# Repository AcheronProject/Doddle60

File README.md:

# Acheron ISO60-SM-S-STM32-MX-TH-WI (Codename "Doddle60")

See [this page](https://gondolindrim.github.io/AcheronDocs/doddle60/intro.html) for the Doddle60PCB documentation.

## Introduction

**Doddle**. *British slang for something easily accomplished*.

The Doddle60 is a 60% plain-style PCB aimed at ISO layout users. It features minimal layout support and no LED backlight support. It runs an STM32F072 processor, USBC connector, ESD protection on both data lines and metallic case discharge, as well as overvoltage and overcurrent protection.

The layout was cherry-picked and hinited to me by Jae of the TopClack channel, an avid ISO user brit.

## Supported layouts

Click [this link](http://www.keyboard-layout-editor.com/#/gists/dfb069e34f7b14d63b03305a79dfc469) for the KLE file for the Doddle60.

## Renders

Click at the images to zoom in.

Renders generated by the [tracespace.io](https://tracespace.io/view/) site.

## Copyright notice

This project is released under the Acheron Open-Hardware License V1.1. For the license, please refer to the LICENCE.md file.

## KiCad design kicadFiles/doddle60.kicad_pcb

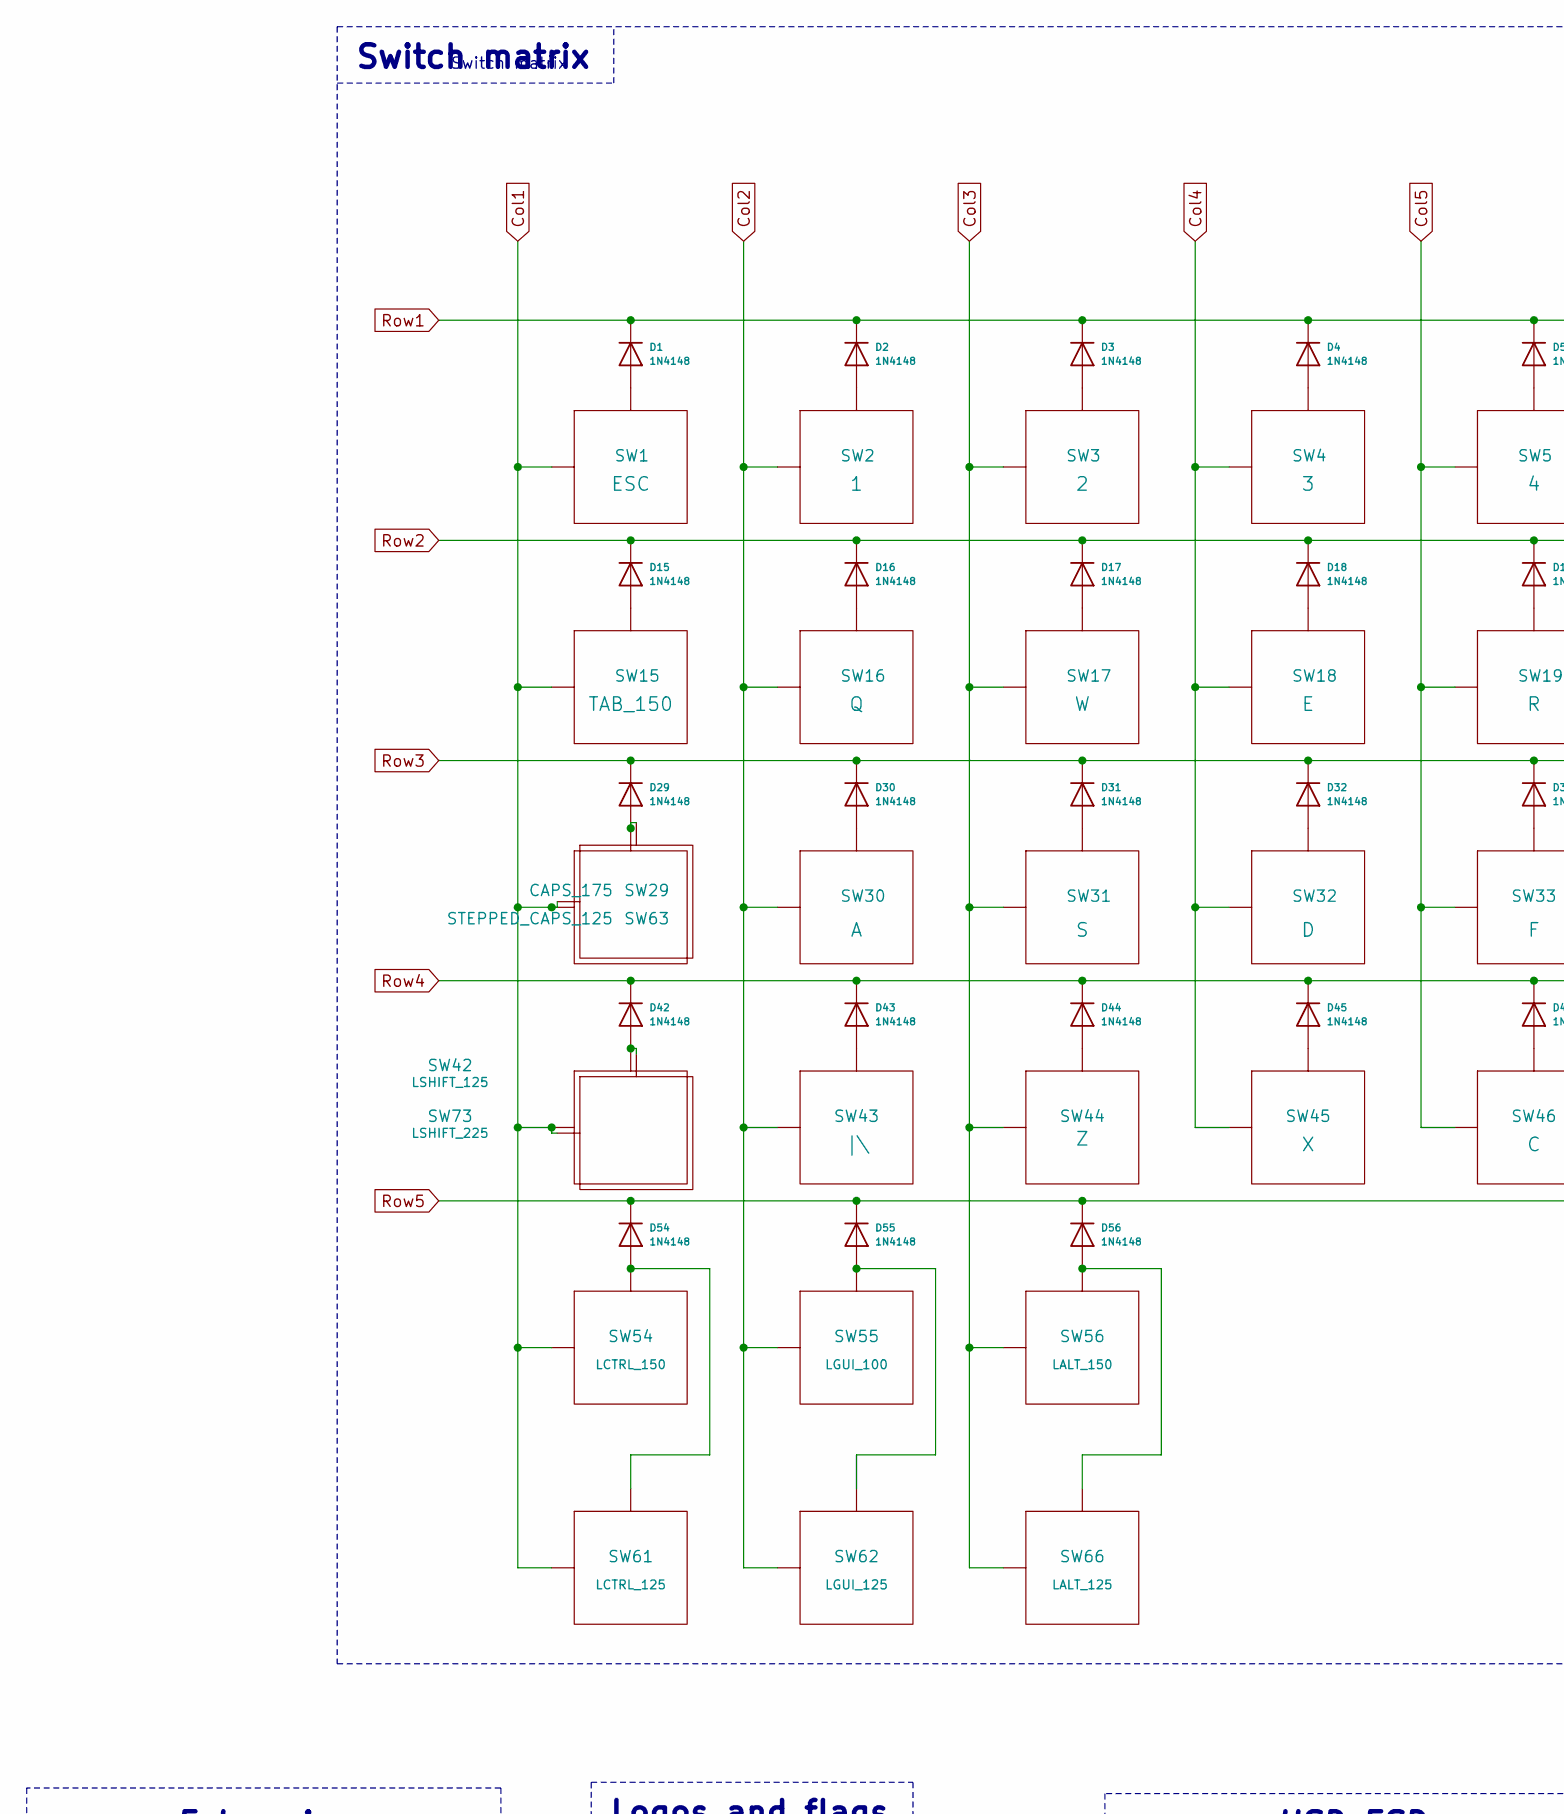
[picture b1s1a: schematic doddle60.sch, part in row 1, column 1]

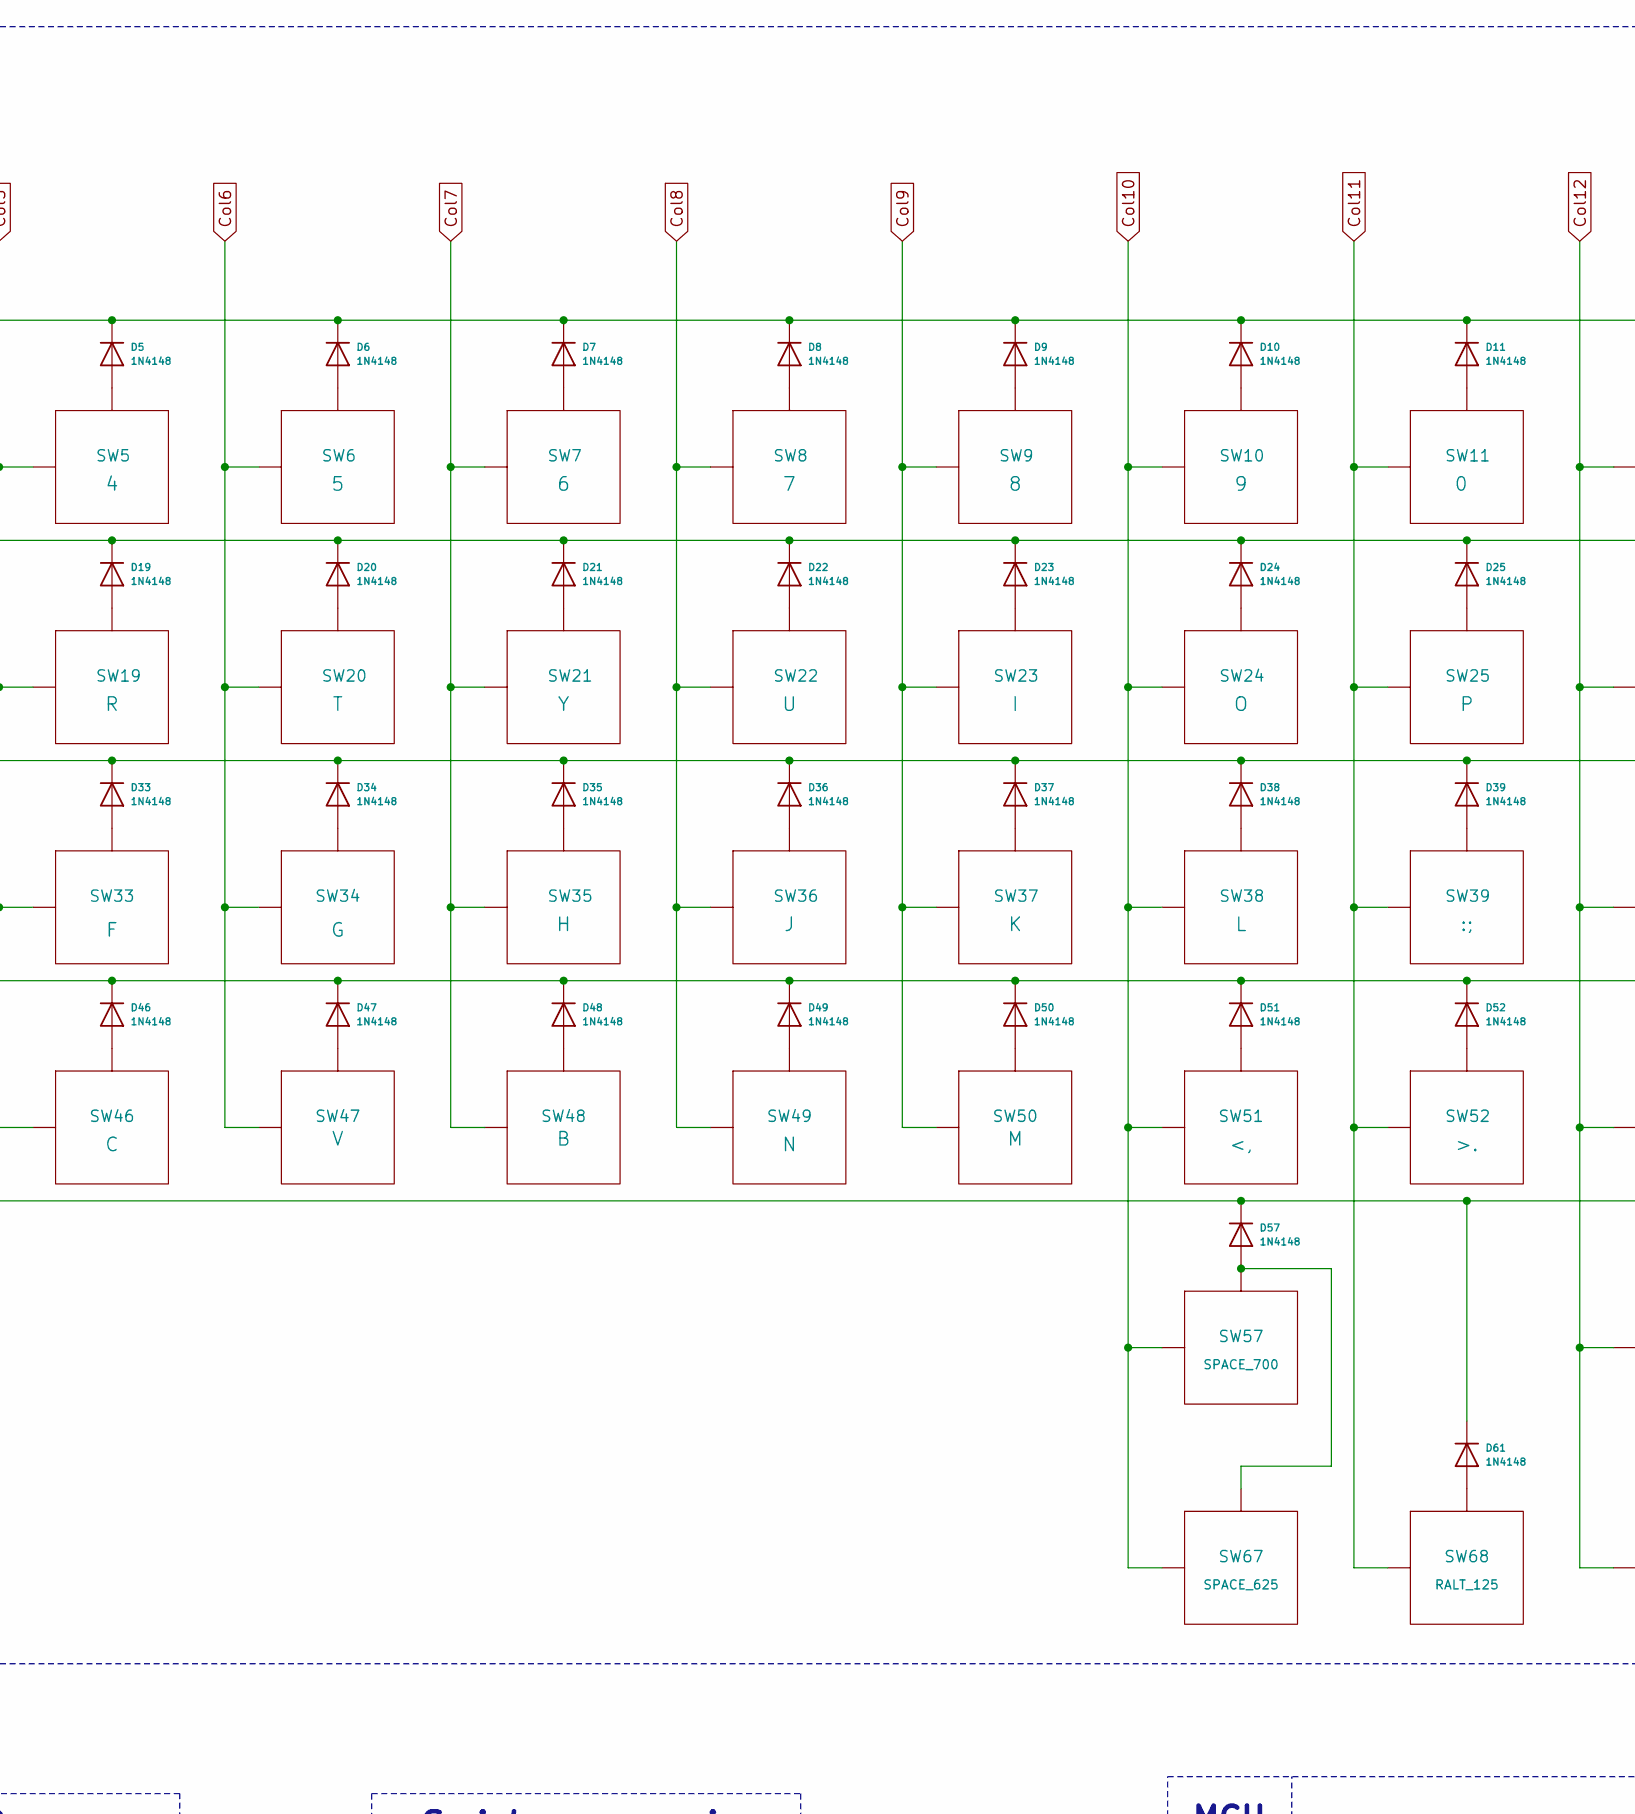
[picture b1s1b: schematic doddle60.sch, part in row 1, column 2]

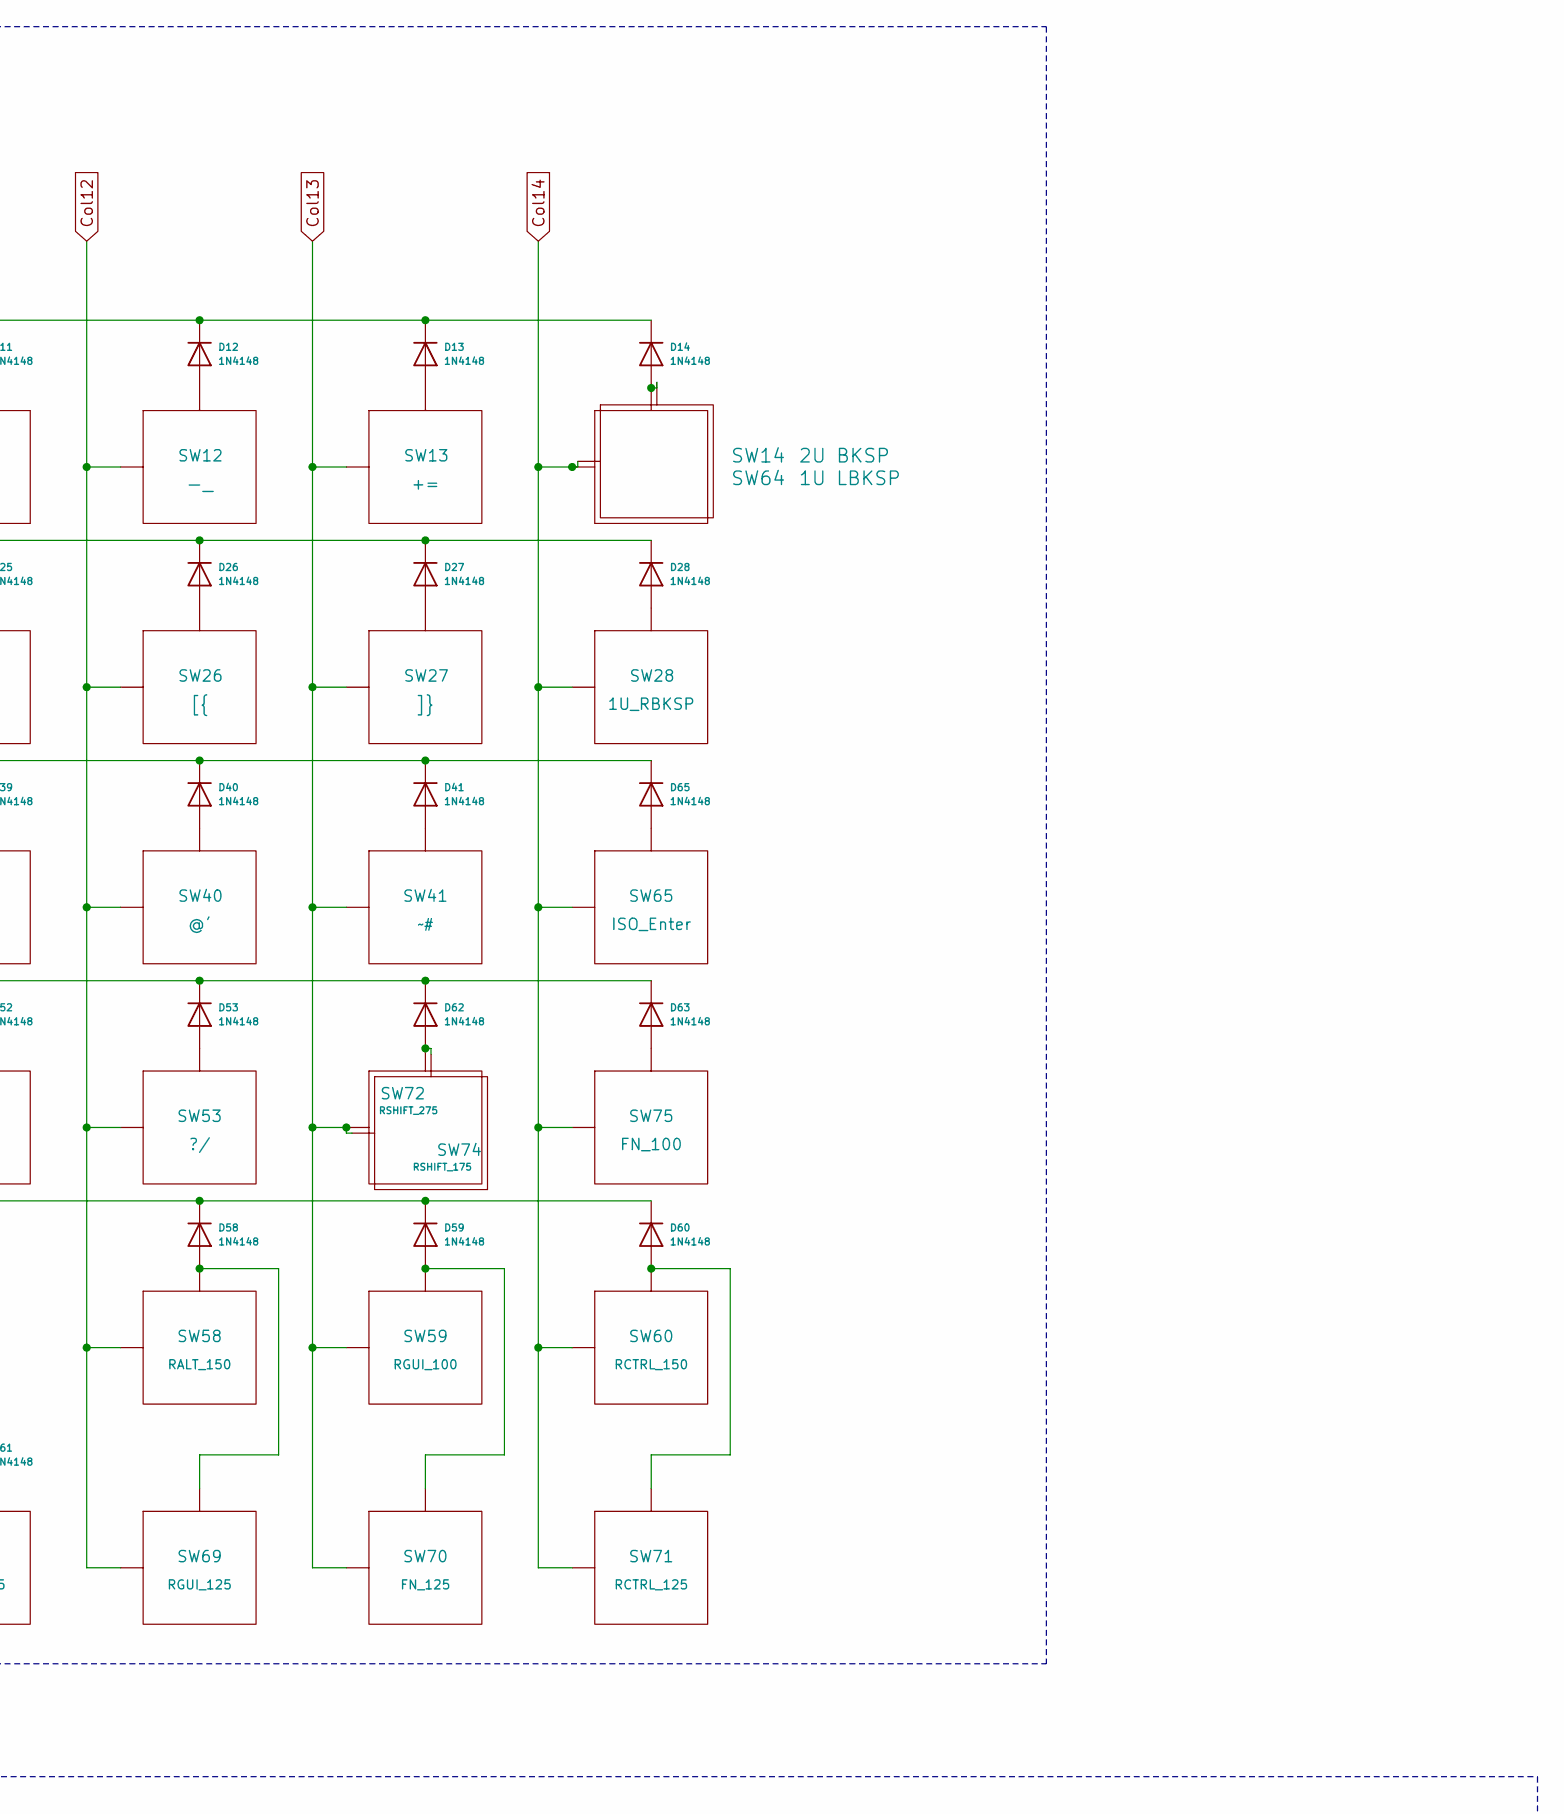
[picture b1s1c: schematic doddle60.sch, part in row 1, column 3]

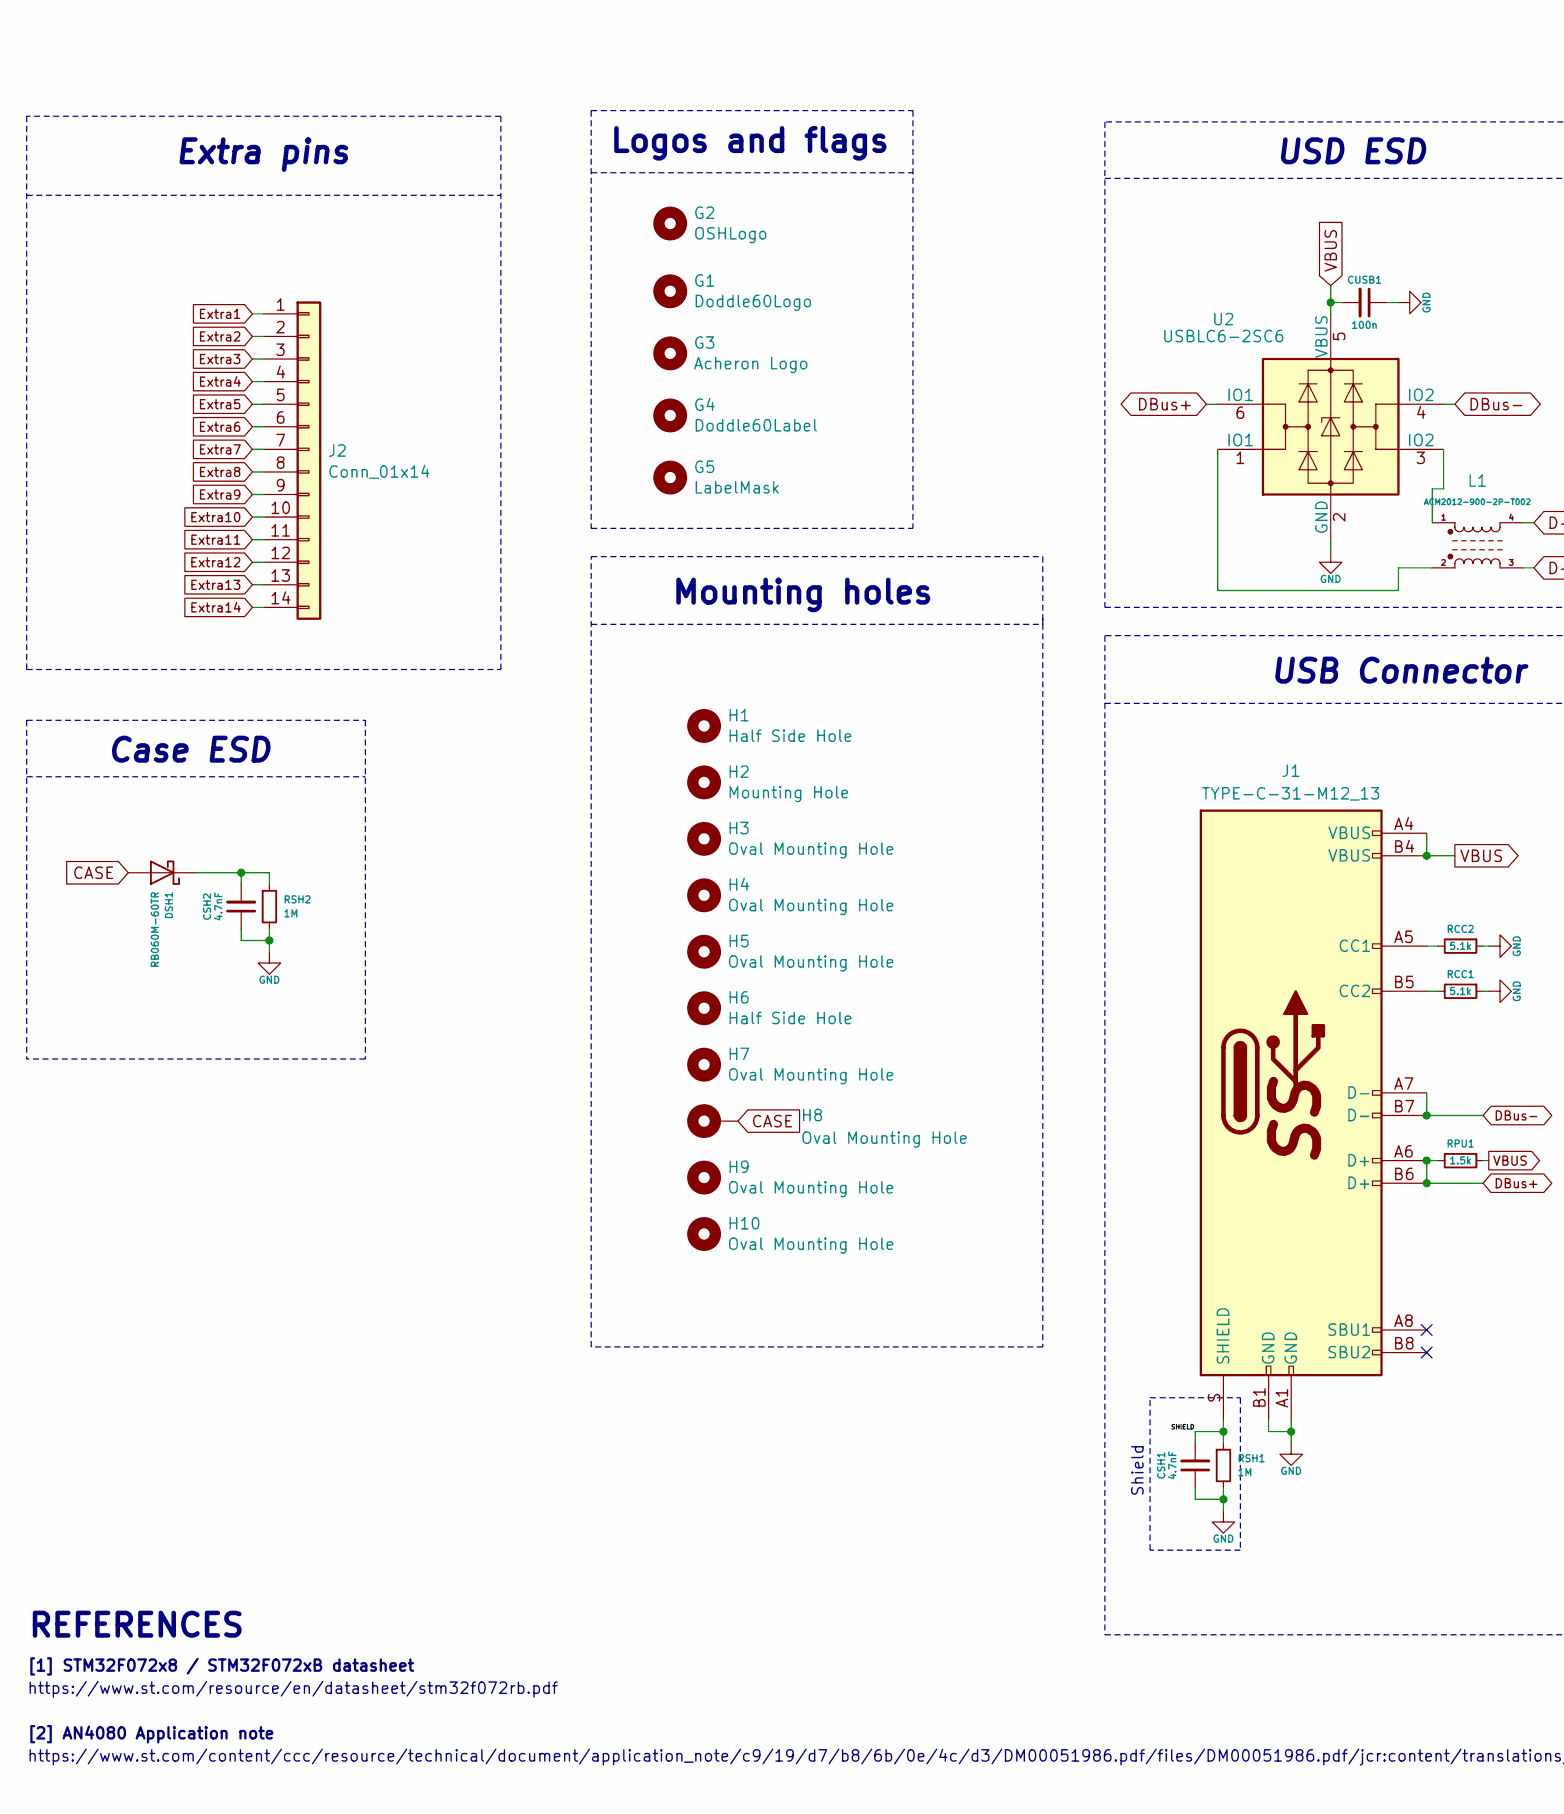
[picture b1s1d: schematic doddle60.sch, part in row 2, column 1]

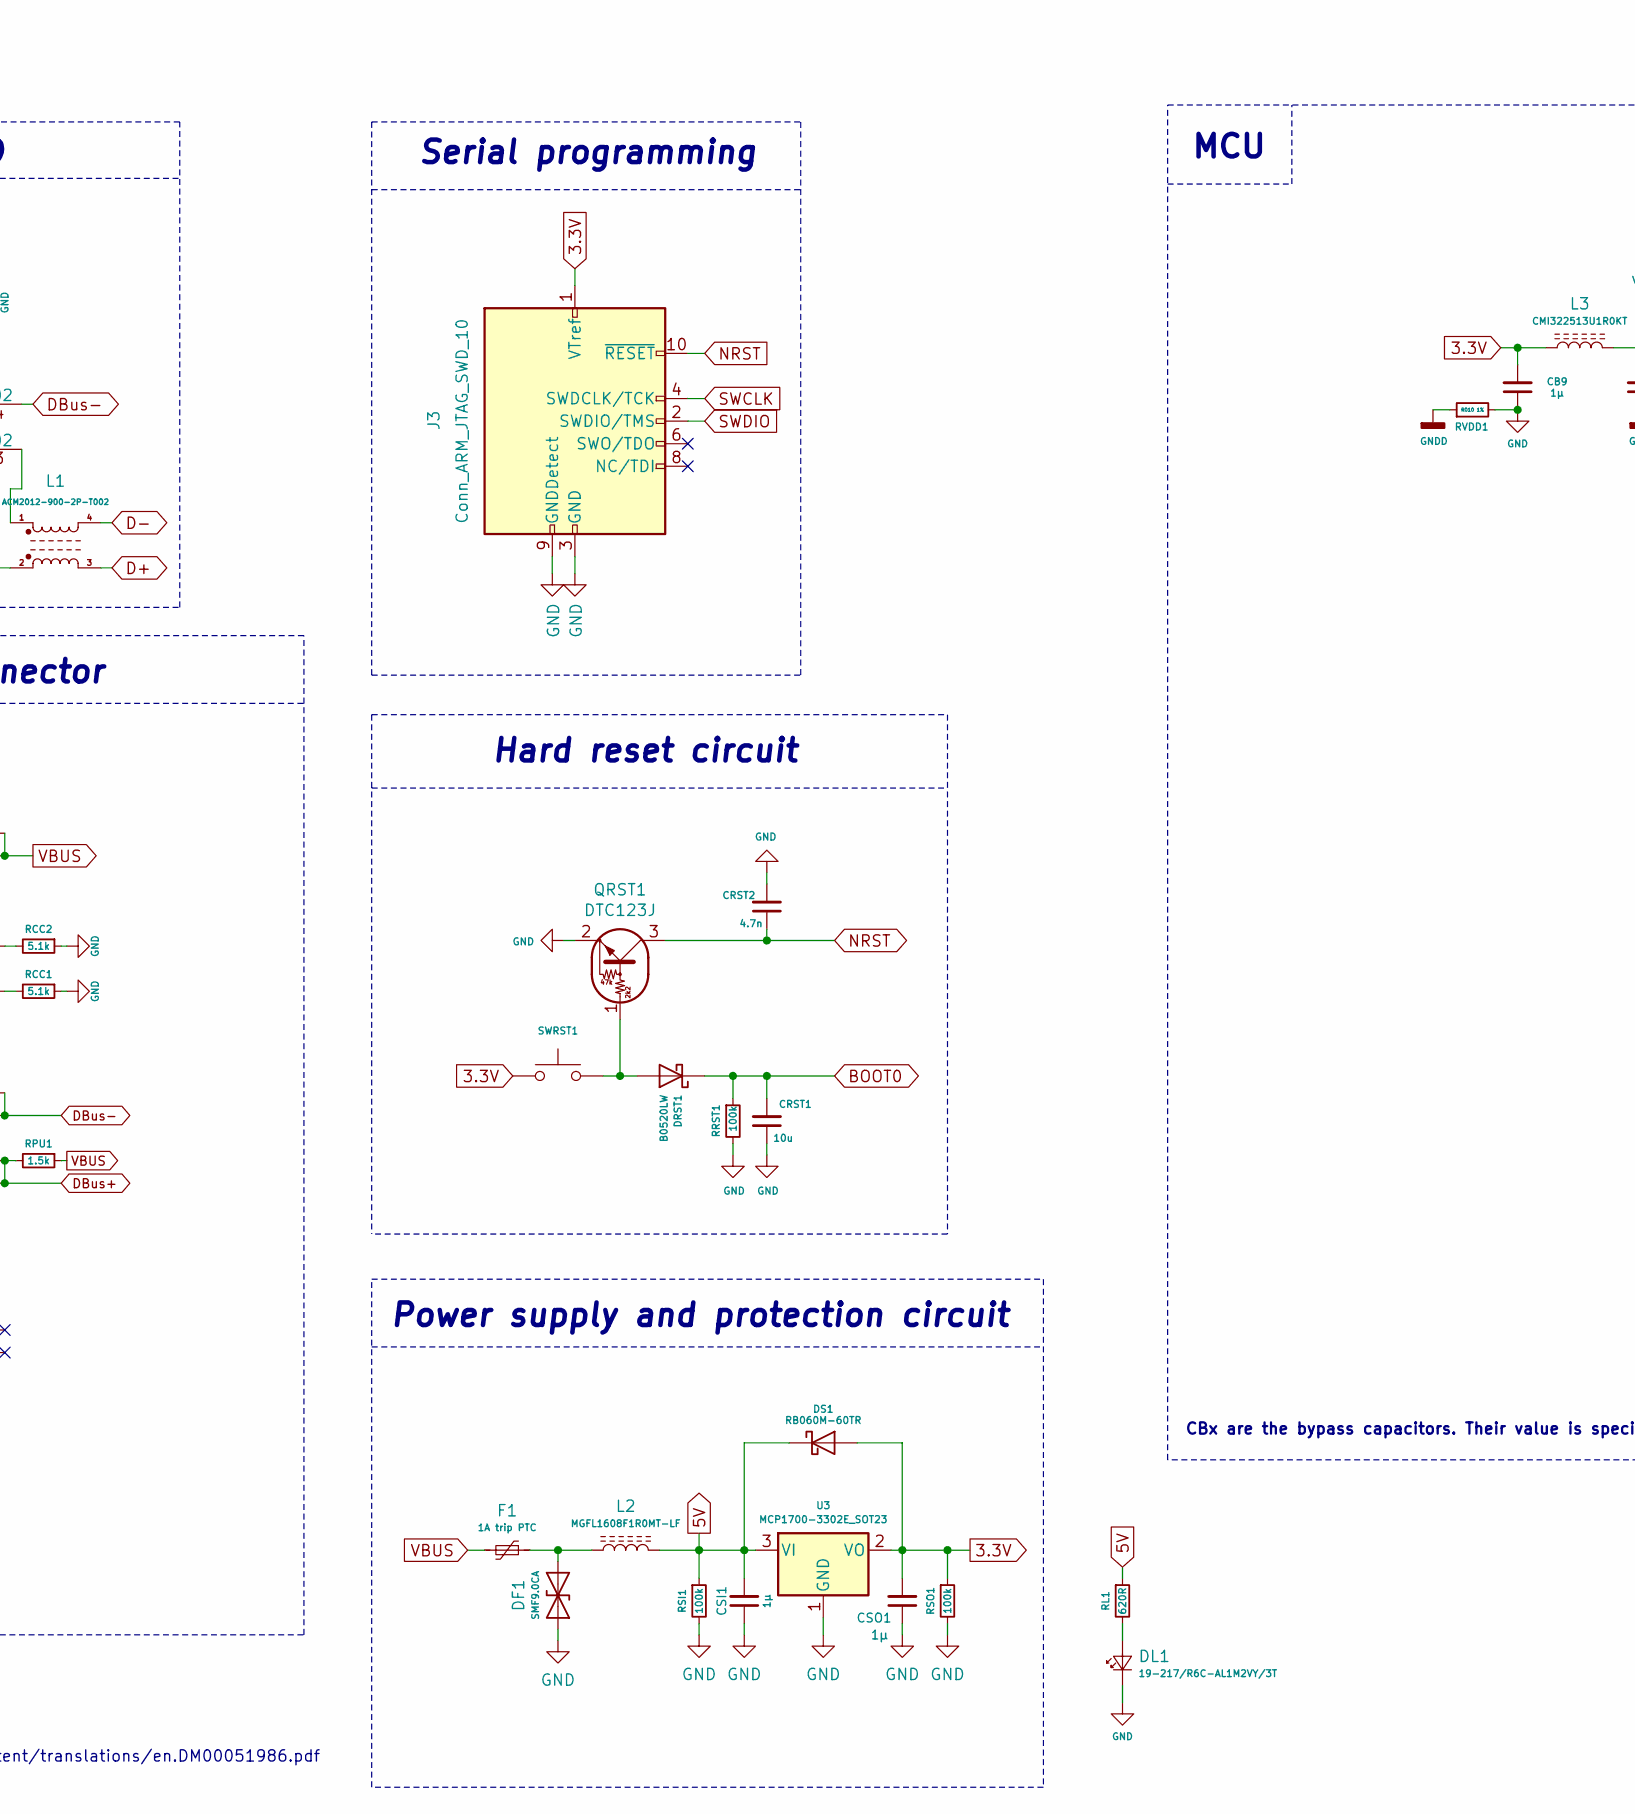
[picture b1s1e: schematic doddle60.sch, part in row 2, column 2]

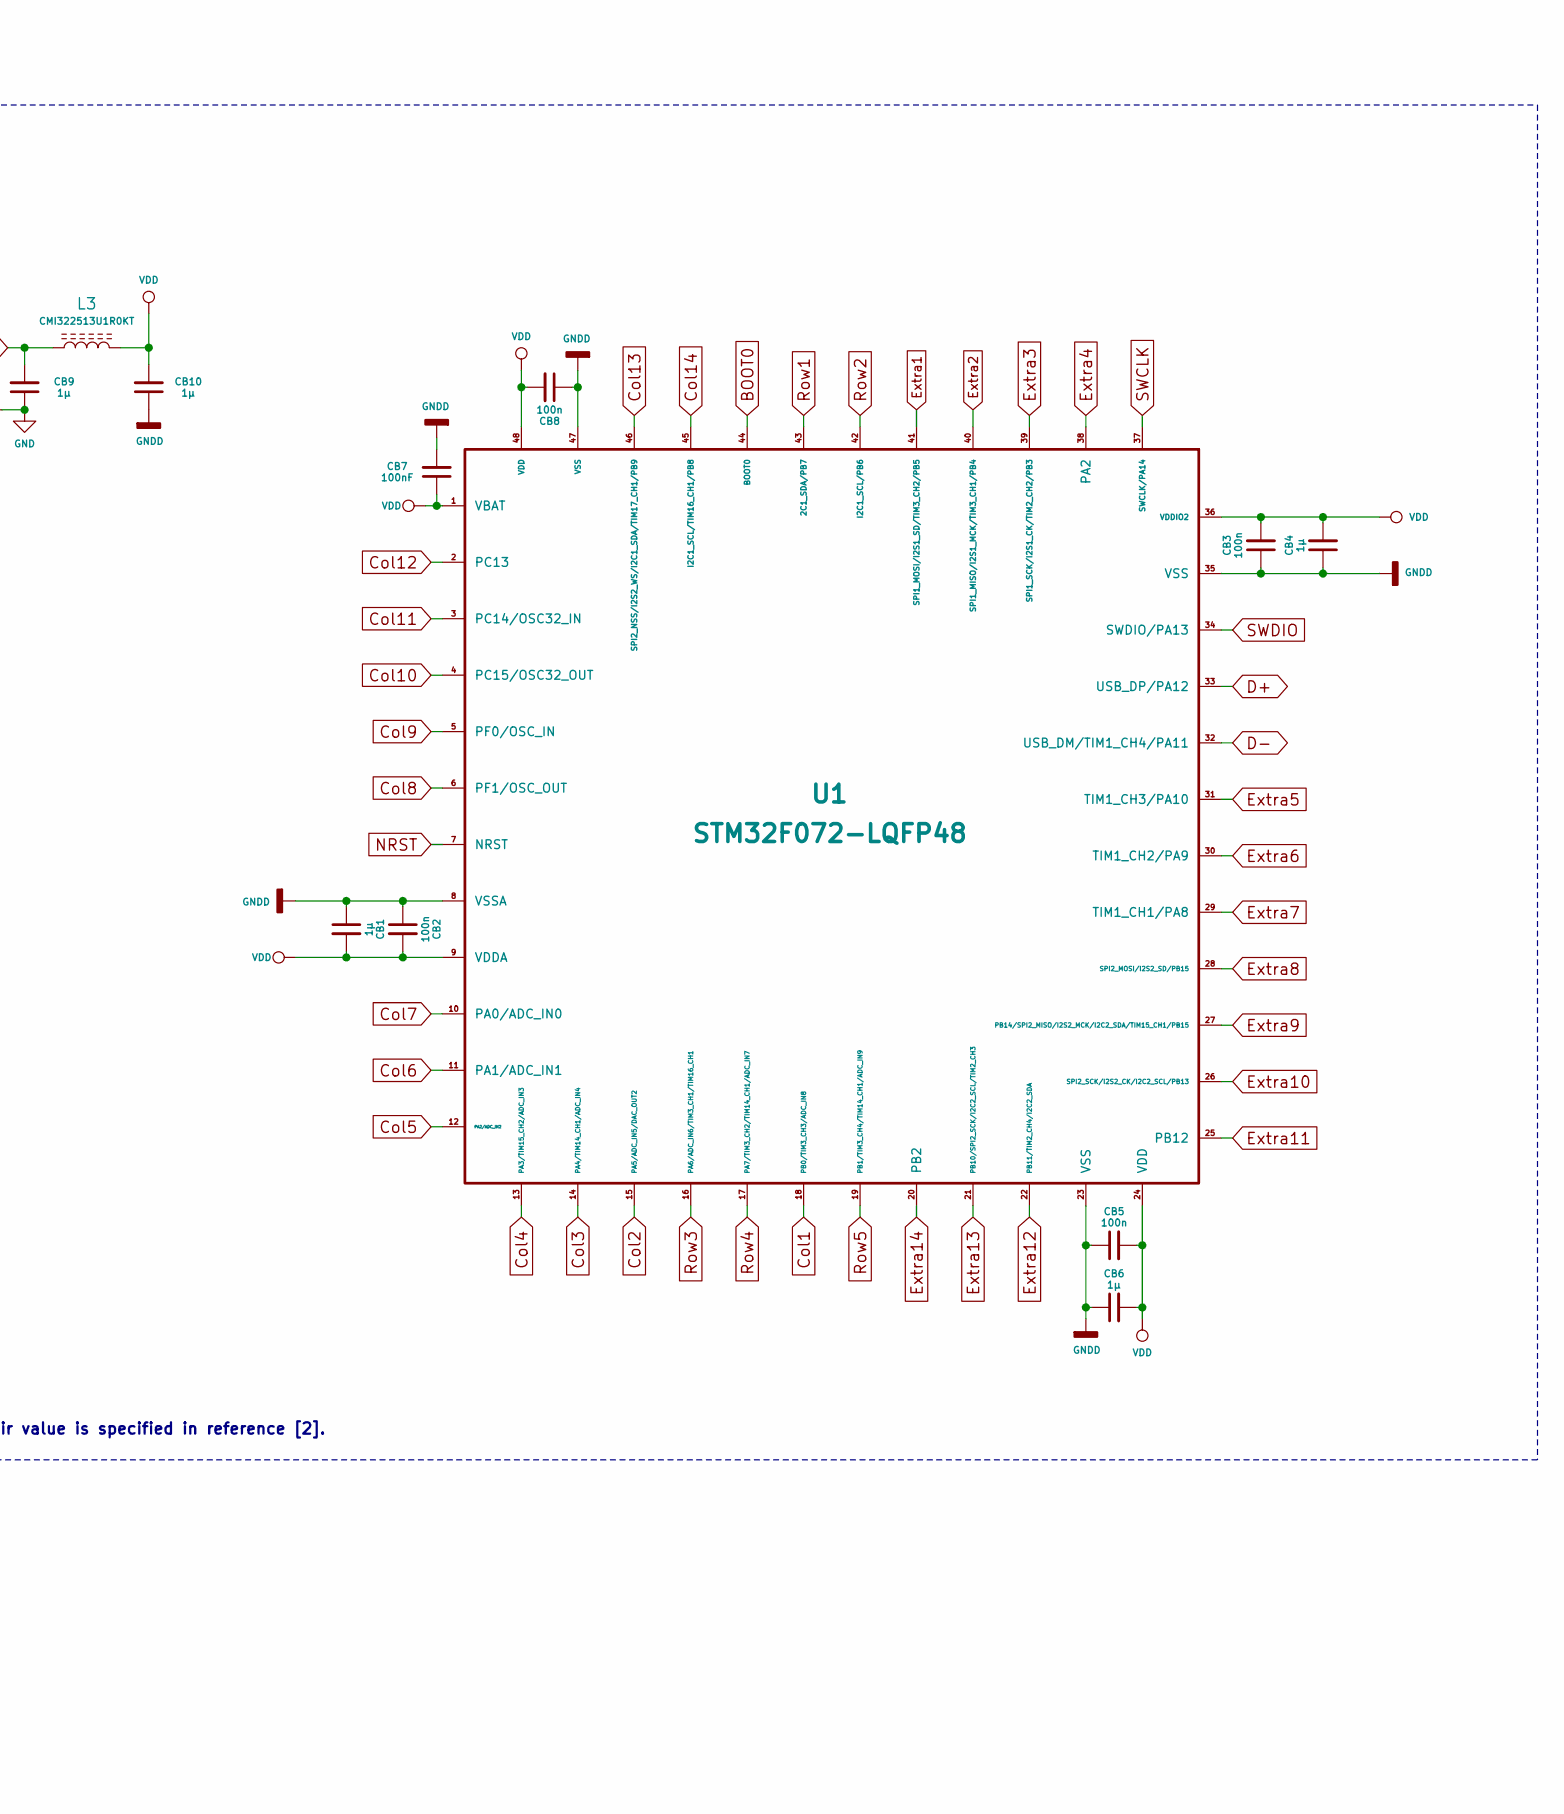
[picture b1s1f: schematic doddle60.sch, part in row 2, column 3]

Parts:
CB1, CB4, CB6: 1µ; C_0402_1005Metric
CB2, CB3, CB5, CB8: 100n; C_0402_1005Metric
CB7: 100nF; C_0402_1005Metric
CB9, CB10: 1µ; C_0805_2012Metric
CRST1: 10u; C_0805_2012Metric_Pad1.15x1.40mm_HandSolder
CRST2: 4.7n; C_0805_2012Metric_Pad1.15x1.40mm_HandSolder
CSH1, CSH2: 4.7nF; C_0805_2012Metric
CSI1: 1µ; C_0805_2012Metric_Pad1.15x1.40mm_HandSolder
CSO1: 1µ; C_0805_2012Metric_Pad1.15x1.40mm_HandSolder
CUSB1: 100n; C_0805_2012Metric_Pad1.15x1.40mm_HandSolder
D1, D2, D3, D4, D5, D6, D7, D8, D9, D10, D11, D12, D13, D14, D15, D16, D17, D18, D19, D20, D21, D22, D23, D24, D25, D26, D27, D28, D29, D30, D31, D32, D33, D34, D35, D36, D37, D38, D39, D40, D41, D42, D43, D44, D45, D46, D47, D48, D49, D50, D51, D52, D53, D54, D55, D56, D57, D58, D59, D60, D61, D62, D63, D65: 1N4148; D_SOD-123
DF1: SMF9.0CA; D_SOD-123_Bidirectional
DL1: 19-217/R6C-AL1M2VY/3T; LED_0603_1608Metric
DRST1: B0520LW; D_SOD-123
DS1: RB060M-60TR; D_SOD-123
DSH1: RB060M-60TR; D_SOD-123
F1: 1A trip PTC; Fuse_1812_4532
G1: Doddle60Logo; doddle60Logo
G2: OSHLogo; osh-logo
G3: Acheron Logo; acheronLong
G4: Doddle60Label; doddle60Label
G5: LabelMask; doddle60LabelMask
H1, H6: Half Side Hole; halfSideHole
H2: Mounting Hole; MoutingHole_Oval_7mm_5.0x2.5mm
H3, H4, H5, H7, H8, H9, H10: Oval Mounting Hole; MoutingHole_Oval_7mm_5.0x2.5mm
J1: TYPE-C-31-M12_13; TYPE-C-31-M-12
J2: Conn_01x14; PinHeader_1x14_P2.54mm_Vertical
J3: Conn_ARM_JTAG_SWD_10
L1: ACM2012-900-2P-T002; ACM2012-2P
L2: MGFL1608F1R0MT-LF; L_0603_1608Metric
L3: CMI322513U1R0KT; L_1210_3225Metric
QRST1: DTC123J; SOT-23
RCC1, RCC2: 5.1k; R_SMD_1026
RL1: 620R; R_SMD_1026
RPU1: 1.5k; R_SMD_1026
RRST1: 100k; R_SMD_1026
RSH1, RSH2: 1M; R_SMD_1026
RSI1: 100k; R_SMD_1026
RSO1: 100k; R_SMD_1026
RVDD1: R010 1%; R_SMD_1026
SW1: ESC; MX100
SW2: 1; MX100
SW3: 2; MX100
SW4: 3; MX100
SW5: 4; MX100
SW6: 5; MX100
SW7: 6; MX100
SW8: 7; MX100
SW9: 8; MX100
SW10: 9; MX100
SW11: 0; MX100
SW12: -_; MX100
SW13: +=; MX100
SW14: 2U BKSP; MX200
SW15: TAB_150; MX150
SW16: Q; MX100
SW17: W; MX100
SW18: E; MX100
SW19: R; MX100
SW20: T; MX100
SW21: Y; MX100
SW22: U; MX100
SW23: I; MX100
SW24: O; MX100
SW25: P; MX100
SW26: [{; MX100
SW27: ]}; MX100
SW28: 1U_RBKSP; MX100
SW29: CAPS_175; MX175
SW30: A; MX100
SW31: S; MX100
SW32: D; MX100
SW33: F; MX100
SW34: G; MX100
SW35: H; MX100
SW36: J; MX100
SW37: K; MX100
SW38: L; MX100
SW39: :;; MX100
SW40: @'; MX100
SW41: ~~#; MX100
SW42: LSHIFT_125; MX125
SW43: |\\; MX100
SW44: Z; MX100
SW45: X; MX100
SW46: C; MX100
SW47: V; MX100
SW48: B; MX100
SW49: N; MX100
SW50: M; MX100
SW51: <,; MX100
SW52: >.; MX100
SW53: ?/; MX100
SW54: LCTRL_150; MX150
SW55: LGUI_100; MX100
SW56: LALT_150; MX150
SW57: SPACE_700; MX700R
SW58: RALT_150; MX150
SW59: RGUI_100; MX100
SW60: RCTRL_150; MX150
SW61: LCTRL_125; MX125
SW62: LGUI_125; MX125
SW63: STEPPED_CAPS_125; MX125
SW64: 1U LBKSP; MX100
SW65: ISO_Enter; MX_ISOEnter_Vertical
SW66: LALT_125; MX125
SW67: SPACE_625; MX625R
SW68: RALT_125; MX125
SW69: RGUI_125; MX125
SW70: FN_125; MX125
SW71: RCTRL_125; MX125
SW72: RSHIFT_275; MX275
SW73: LSHIFT_225; MX225
SW74: RSHIFT_175; MX175
SW75: FN_100; MX100
SWRST1: SW_Push; smdPushBtn
U1: STM32F072-LQFP48; LQFP-48_7x7mm_P0.5mm
U2: USBLC6-2SC6; SOT-23-6
U3: MCP1700-3302E_SOT23; SOT-23

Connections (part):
3.3V: CB9.2, CSO1.2, DS1.2 (A), J3.1 (VTref), L3.1, RSO1.1, SWRST1.1, U3.2 (VO)
5V: CSI1.2, DS1.1 (K), L2.2, RL1.1, RSI1.1, U3.3 (VI)
/SHIELD: CSH1.2, J1.S (SHIELD), RSH1.1
BOOT0: CRST1.2, DRST1.1 (K), RRST1.1, U1.44 (BOOT0)
CASE: DSH1.2 (A), H8.1
Col1: SW1.1 (Col), SW15.1 (Col), SW29.1 (Col), SW42.1 (Col), SW54.1 (Col), SW61.1 (Col), SW63.1 (Col), SW73.1 (Col), U1.18 (PB0/TIM3_CH3/ADC_IN8)
Col2: SW2.1 (Col), SW16.1 (Col), SW30.1 (Col), SW43.1 (Col), SW55.1 (Col), SW62.1 (Col), U1.15 (PA5/ADC_IN5/DAC_OUT2)
Col3: SW3.1 (Col), SW17.1 (Col), SW31.1 (Col), SW44.1 (Col), SW56.1 (Col), SW66.1 (Col), U1.14 (PA4/TIM14_CH1/ADC_IN4)
Col4: SW4.1 (Col), SW18.1 (Col), SW32.1 (Col), SW45.1 (Col), U1.13 (PA3/TIM15_CH2/ADC_IN3)
Col5: SW5.1 (Col), SW19.1 (Col), SW33.1 (Col), SW46.1 (Col), U1.12 (PA2/ADC_IN2)
Col6: SW6.1 (Col), SW20.1 (Col), SW34.1 (Col), SW47.1 (Col), U1.11 (PA1/ADC_IN1)
Col7: SW7.1 (Col), SW21.1 (Col), SW35.1 (Col), SW48.1 (Col), U1.10 (PA0/ADC_IN0)
Col8: SW8.1 (Col), SW22.1 (Col), SW36.1 (Col), SW49.1 (Col), U1.6 (PF1/OSC_OUT)
Col9: SW9.1 (Col), SW23.1 (Col), SW37.1 (Col), SW50.1 (Col), U1.5 (PF0/OSC_IN)
Col10: SW10.1 (Col), SW24.1 (Col), SW38.1 (Col), SW51.1 (Col), SW57.1 (Col), SW67.1 (Col), U1.4 (PC15/OSC32_OUT)
Col11: SW11.1 (Col), SW25.1 (Col), SW39.1 (Col), SW52.1 (Col), SW68.1 (Col), U1.3 (PC14/OSC32_IN)
Col12: SW12.1 (Col), SW26.1 (Col), SW40.1 (Col), SW53.1 (Col), SW58.1 (Col), SW69.1 (Col), U1.2 (PC13)
Col13: SW13.1 (Col), SW27.1 (Col), SW41.1 (Col), SW59.1 (Col), SW70.1 (Col), SW72.1 (Col), SW74.1 (Col), U1.46 (SPI2_NSS/I2S2_WS/I2C1_SDA/TIM17_CH1/PB9)
Col14: SW14.1 (Col), SW28.1 (Col), SW60.1 (Col), SW64.1 (Col), SW65.1 (Col), SW71.1 (Col), SW75.1 (Col), U1.45 (I2C1_SCL/TIM16_CH1/PB8)
D+: L1.3, U1.33 (USB_DP/PA12)
D-: L1.4, U1.32 (USB_DM/TIM1_CH4/PA11)
DBus+: J1.A6 (D+), J1.B6 (D+), RPU1.2, U2.6 (IO1)
DBus-: J1.A7 (D-), J1.B7 (D-), U2.4 (IO2)
Extra1: J2.1, U1.41 (SPI1_MOSI/I2S1_SD/TIM3_CH2/PB5)
Extra2: J2.2, U1.40 (SPI1_MISO/I2S1_MCK/TIM3_CH1/PB4)
Extra3: J2.3, U1.39 (SPI1_SCK/I2S1_CK/TIM2_CH2/PB3)
Extra4: J2.4, U1.38 (PA2)
Extra5: J2.5, U1.31 (TIM1_CH3/PA10)
Extra6: J2.6, U1.30 (TIM1_CH2/PA9)
Extra7: J2.7, U1.29 (TIM1_CH1/PA8)
Extra8: J2.8, U1.28 (SPI2_MOSI/I2S2_SD/PB15)
Extra9: J2.9, U1.27 (PB14/SPI2_MISO/I2S2_MCK/I2C2_SDA/TIM15_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)
Extra10: J2.10, U1.26 (SPI2_SCK/I2S2_CK/I2C2_SCL/PB13)
Extra11: J2.11, U1.25 (PB12)
Extra12: J2.12, U1.22 (PB11/TIM2_CH4/I2C2_SDA)
Extra13: J2.13, U1.21 (PB10/SPI2_SCK/I2C2_SCL/TIM2_CH3)
Extra14: J2.14, U1.20 (PB2)
GND: CB9.1, CRST1.1, CRST2.2, CSH1.1, CSH2.1, CSI1.1, CSO1.1, CUSB1.1, DF1.2 (A2), DL1.1 (K), J1.A1 (GND), J1.B1 (GND), J3.3 (GND), J3.5 (GND), J3.9 (GNDDetect), QRST1.2 (E), RCC1.1, RCC2.1, RRST1.2, RSH1.2, RSH2.2, RSI1.2, RSO1.2, RVDD1.2, U2.2 (GND), U3.1 (GND)
GNDD: CB1.1, CB2.1, CB3.1, CB4.1, CB5.1, CB6.1, CB7.2, CB8.1, CB10.1, RVDD1.1, U1.8 (VSSA), U1.23 (VSS), U1.35 (VSS), U1.47 (VSS)
NRST: CRST2.1, J3.10 (~RESET~), QRST1.3 (C), U1.7 (NRST)
unnamed: CSH2.2, DSH1.1 (K), RSH2.1
unnamed: D1.2 (A), SW1.2 (Row)
unnamed: D2.2 (A), SW2.2 (Row)
unnamed: D3.2 (A), SW3.2 (Row)
unnamed: D4.2 (A), SW4.2 (Row)
unnamed: D5.2 (A), SW5.2 (Row)
unnamed: D6.2 (A), SW6.2 (Row)
unnamed: D7.2 (A), SW7.2 (Row)
unnamed: D8.2 (A), SW8.2 (Row)
unnamed: D9.2 (A), SW9.2 (Row)
unnamed: D10.2 (A), SW10.2 (Row)
unnamed: D11.2 (A), SW11.2 (Row)
unnamed: D12.2 (A), SW12.2 (Row)
unnamed: D13.2 (A), SW13.2 (Row)
unnamed: D14.2 (A), SW14.2 (Row), SW64.2 (Row)
unnamed: D15.2 (A), SW15.2 (Row)
unnamed: D16.2 (A), SW16.2 (Row)
unnamed: D17.2 (A), SW17.2 (Row)
unnamed: D18.2 (A), SW18.2 (Row)
unnamed: D19.2 (A), SW19.2 (Row)
unnamed: D20.2 (A), SW20.2 (Row)
unnamed: D21.2 (A), SW21.2 (Row)
unnamed: D22.2 (A), SW22.2 (Row)
unnamed: D23.2 (A), SW23.2 (Row)
unnamed: D24.2 (A), SW24.2 (Row)
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
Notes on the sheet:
Hard reset circuit
Power supply and protection circuit
Logos and flags
Serial programming
[1] STM32F072x8 / STM32F072xB datasheet
REFERENCES
https://www.st.com/resource/en/datasheet/stm32f072rb.pdf
[2] AN4080 Application note
https://www.st.com/content/ccc/resource/technical/document/application_note/c9/19/d7/b8/6b/0e/4c/d3/DM00051986.pdf/files/DM00051986.pdf/jcr:content/translations/en.DM00051986.pdf
MCU
USB Connector
Shield
USD ESD
CBx are the bypass capacitors. Their value is specified in reference [2].
Case ESD
Switch matrix
Mounting holes
Extra pins

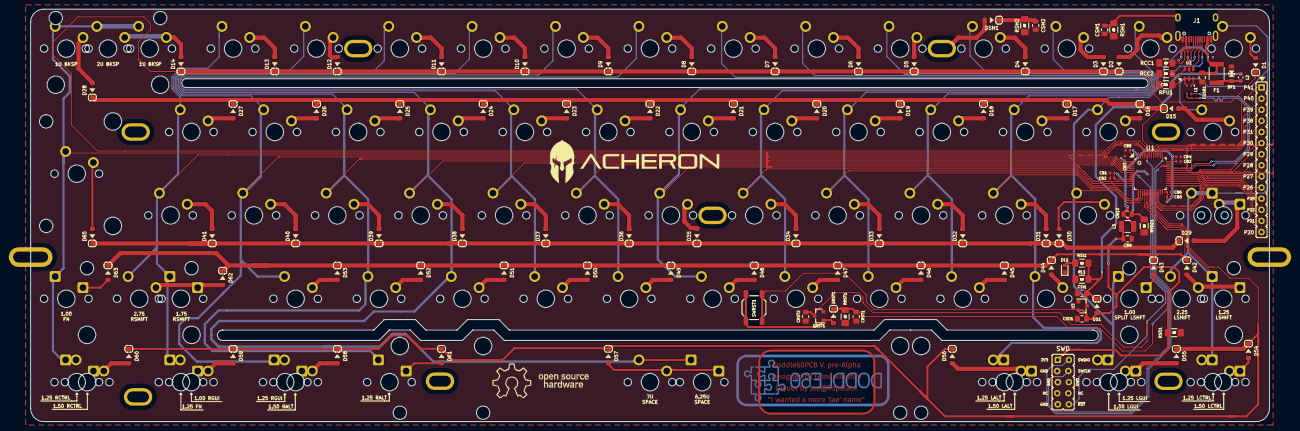
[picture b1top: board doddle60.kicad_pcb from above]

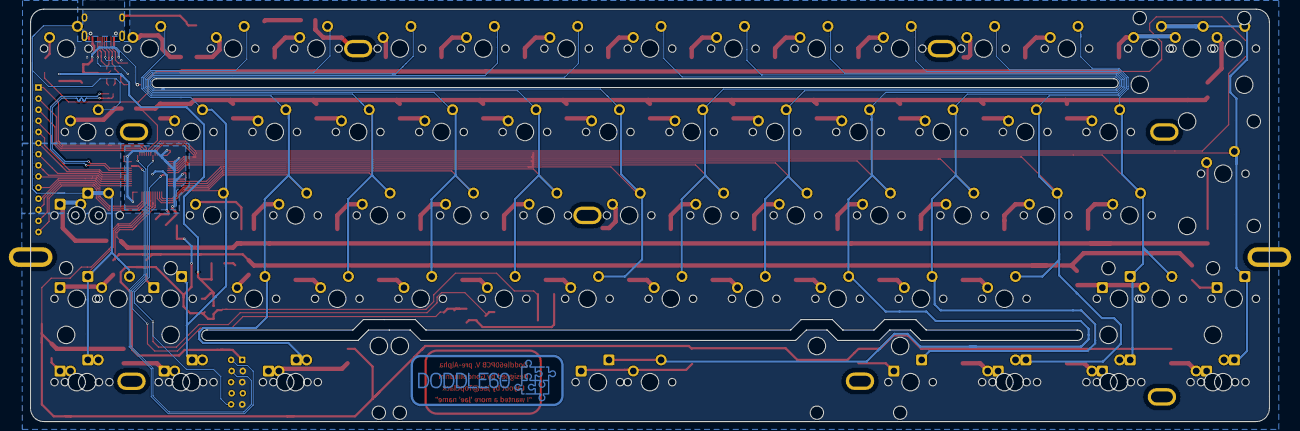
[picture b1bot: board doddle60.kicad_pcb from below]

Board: 2 copper layers, 283.0 x 94.2 mm, 198 parts (7 on the bottom side), 121 nets.

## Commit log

2019-10-25 Incorporate feedback from GeekHack IC
    - There was a big feedback from the community on the GeekHack Interest Check thread (https://geekhack.org/index.php?topic=103057), mainly the lack of split right shift conpatibility and 2.25 left shi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
    - Some tweaks were made in the LDO area. Input and output resistors were added to discharge all the capacitors once the PCB is not energized. Also the value os CSO1 was changed from 100nF to 1uF for 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
2019-10-25 Run DRC
    - DRC was ran and issues solved
2019-10-25 Update KLE and renders
2019-10-25 Add TVS, diff impedance, pi filter
    - A TVS diode was added to the VBUS power rail for more stability and voltage clamping;
    - A differential mode choke was added to the data lines;
    - A pi filter with a differential mode choke was added to the MCU power circuit for isolation and stability
2019-11-05 Implement filters, TVS and LED
    - The pi filter for VDD and GNDD was implemented; the common mode choke
    added to the schematic on the last commit was deemed unnecessary and
    thence removed
    - The TVS and choke for VBUS-5V was implemented;
    - The common mode choke for USB data lines was added
2019-11-05 Add layout indicator silkscreen
2019-11-05 Refresh renders
2019-11-11 Update renders
